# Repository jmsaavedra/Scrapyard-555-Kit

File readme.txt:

board (.brd) and schematic (.sch) files for the 555 timer based DIY noise maker kit from Scrapyard Challenge.

http://scrapyardchallenge.com

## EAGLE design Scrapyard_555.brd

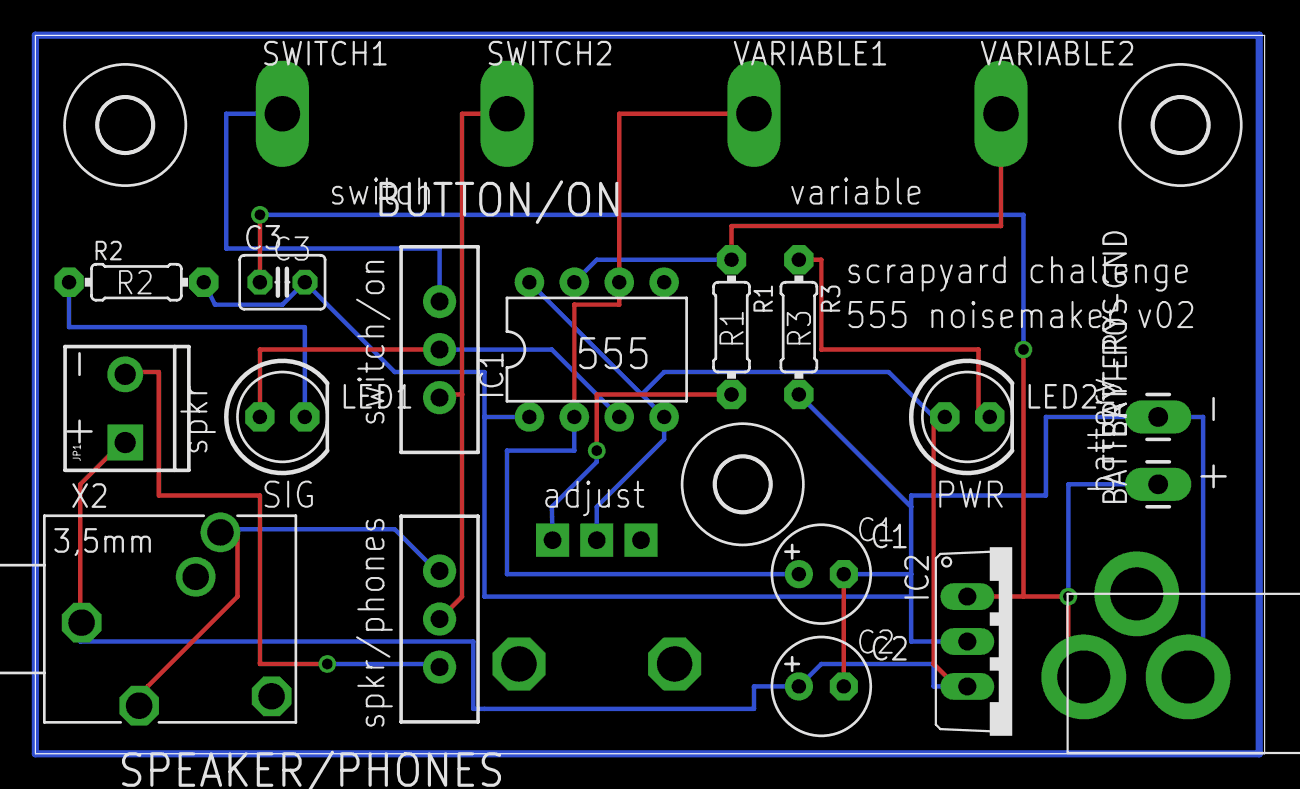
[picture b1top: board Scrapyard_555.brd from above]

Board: 2 copper layers, 69.5 x 40.6 mm, 25 parts (0 on the bottom side), 13 nets.

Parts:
BATTERY-GND: M01PTH_LONGPAD; 1X01_LONGPAD
BATTERY-POS: M01PTH_LONGPAD; 1X01_LONGPAD
BUTTON/ON: SWITCH-SPDT_KIT
C1: 4.7uF; E2,5-6
C2: 10uF; E2,5-6
C3: 0.1uF; C025-030X050
IC1: NE555N; DIL08-ROUND
IC2: 788TV; TO220V
JP1: SCREWTERMINAL-3.5MM-2_LOCK
LED1, LED2: LED5MM
R1: 220; 0204/7
R2, R3: 1k; 0204/7
SPEAKER/PHONES: SWITCH-SPDT_KIT
SWITCH1, SWITCH2: TPPAD1-20Y; P1-20Y
U$1: 2.1MMJACKTHM; PJ-102A
U$5, U$6, U$10: 3,0
U$9: 10k; ALPS_POT
VARIABLE1, VARIABLE2: TPPAD1-20Y; P1-20Y
X2: PG203J

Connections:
5V: C2.+, IC1.4, IC1.8, IC2.3, JP1.1, LED2.A, U$9.P$2, X2.1
GND: BATTERY-GND.1, C1.-, C2.-, C3.2, IC1.1, IC2.2, R2.2, R3.2, U$1.RING
unnamed: C1.+, IC1.2, IC1.6, VARIABLE1.TP
unnamed: BATTERY-POS.1, C3.1, IC2.1, U$1.TIP
unnamed: BUTTON/ON.2, IC1.3, LED1.A
unnamed: LED1.K, R2.1
unnamed: IC1.7, R1.1, VARIABLE2.TP
unnamed: JP1.2, SPEAKER/PHONES.1
unnamed: SPEAKER/PHONES.3, X2.2, X2.5
unnamed: BUTTON/ON.3, SPEAKER/PHONES.2, SWITCH2.TP
unnamed: BUTTON/ON.1, SWITCH1.TP
unnamed: R1.2, U$9.P$3
unnamed: LED2.K, R3.1

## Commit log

2011-11-21 readme
2011-11-21 board and schematic
2011-11-21 added battery input and powerOn LED
2011-11-21 new board with final components, unplaced, unrouted
2011-11-21 read me updated
2012-04-27 v02 updated
